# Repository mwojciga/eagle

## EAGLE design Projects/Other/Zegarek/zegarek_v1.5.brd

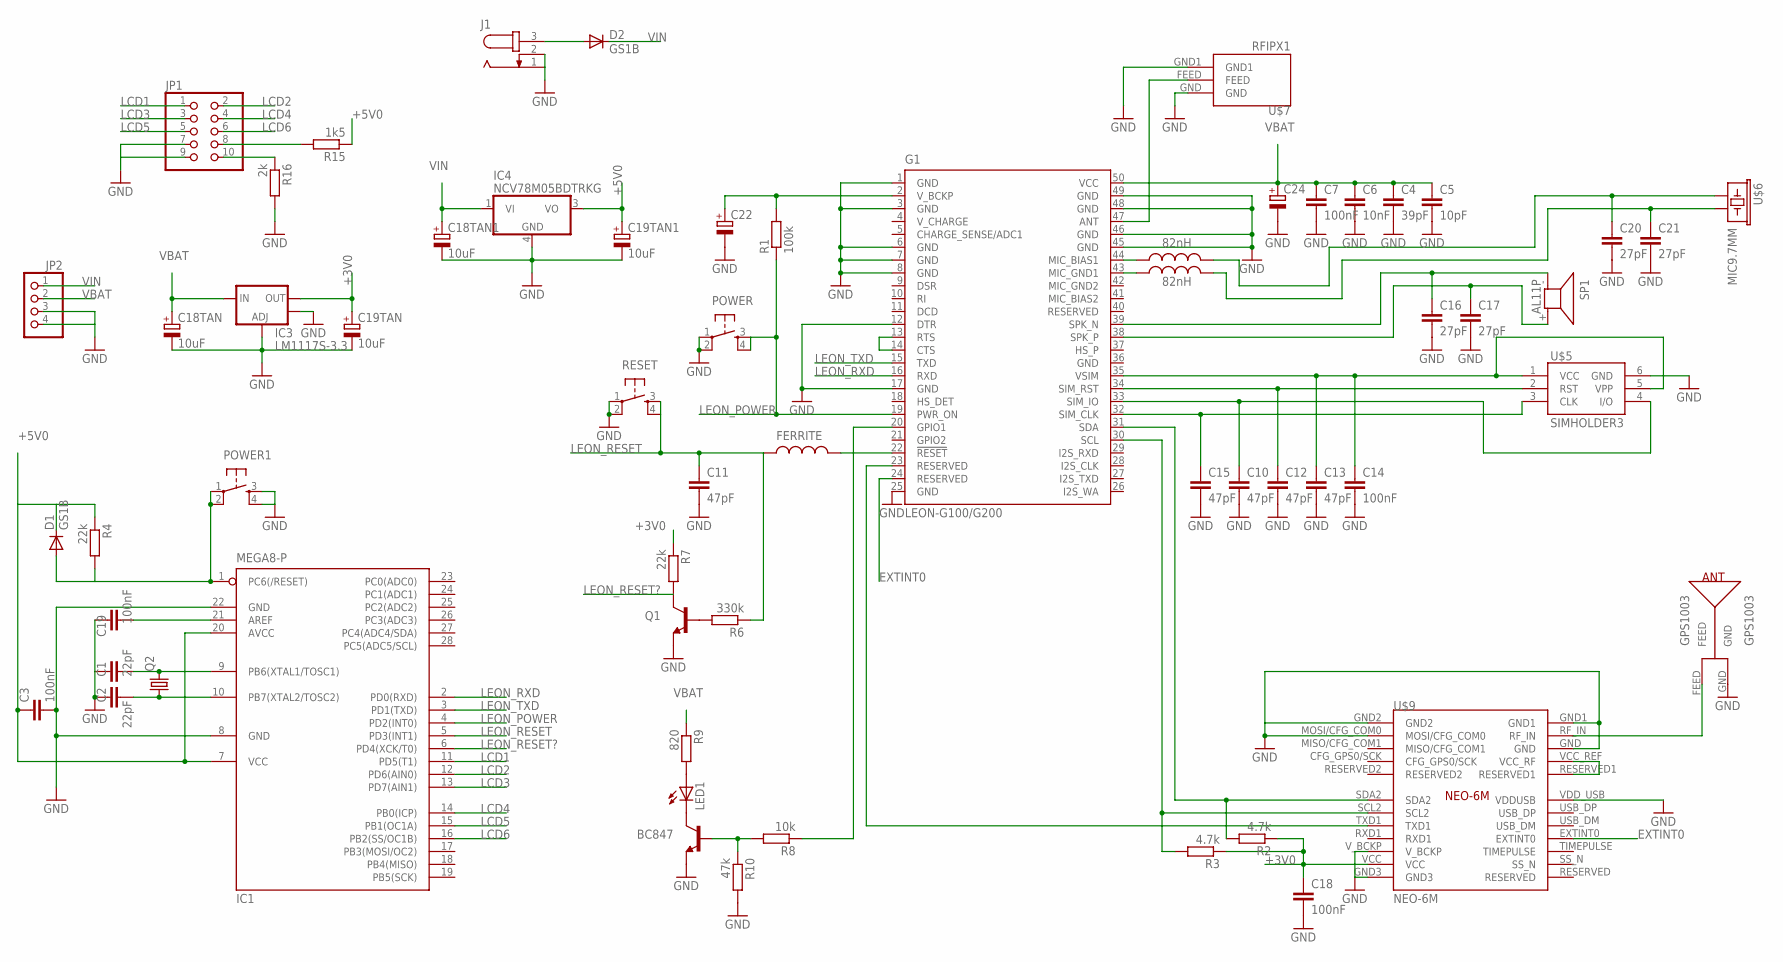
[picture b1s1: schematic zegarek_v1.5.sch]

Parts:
BC847: TRANSISTOR_NPNSOT23; SOT23
C1, C2: 22pF; C0805
C3, C7, C14, C18, C19: 100nF; C0805
C4: 39pF; C0805
C5: 10pF; C0805
C6: 10nF; C0805
C10, C11, C12, C13, C15: 47pF; C0805
C16, C17, C20, C21: 27pF; C0805
C18TAN, C18TAN1, C19TAN, C19TAN1: 10uF; SMC_A
C22, C24: CPOL-EUE2-5; E2-5
D1, D2: GS1B; DO214AC
FERRITE: INDUCTOR0805; 0805
FERRITE1, FERRITE2: 82nH; 0805
G1: LEON-G100/G200
GPS1003: GPS1003
IC1: MEGA8-P; DIL28-3
IC3: LM1117S-3.3; SOT223
IC4: NCV78M05BDTRKG; DPACK_3
J1: JACK-PLUG0; SPC4077
JP1: PINHD-2X5; 2X05
JP2: PINHD-1X4; 1X04
LED1: LEDSMT1206; 1206
POWER, POWER1: TAC_SWITCHSMD; TACTILE_SWITCH_SMD
Q1: TRANSISTOR_NPNSOT23; SOT23
Q2: CRYSTALHC49S; HC49/S
R1: 100k; R0805
R2, R3: 4.7k; R0805
R4, R7: 22k; R0805
R6: 330k; R0805
R8: 10k; R0805
R9: 820; R0805
R10: 47k; R0805
R15: 1k5; R0805
R16: 2k; R0805
RESET: TAC_SWITCHSMD; TACTILE_SWITCH_SMD
SP1: AL11P
U$5: SIMHOLDER3
U$6: MIC9.7MM; MIC-9.7MM
U$7: RFIPX1; RF-IPX1
U$9: NEO-6M

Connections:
+3V0: C18.1, C19TAN.+, IC3.2 (OUT), R2.1, R3.1, R7.1, U$9.VCC
+5V0: C3.1, C19TAN1.+, D1.C, IC1.7 (VCC), IC1.20 (AVCC), IC4.3 (VO), R4.1, R15.1
EXTINT0: G1.24 (RESERVED), U$9.EXTINT0
GND: BC847.2 (E), C1.1, C2.1, C3.2, C4.2, C5.2, C6.2, C7.2, C10.2, C11.2, C12.2, C13.2, C14.2, C15.2, C16.2, C17.2, C18.2, C18TAN.-, C18TAN1.-, C19.2, C19TAN.-, C19TAN1.-, C20.2, C21.2, C22.-, C24.-, G1.1 (GND), G1.3 (GND), G1.6 (GND), G1.7 (GND), G1.8 (GND), G1.12 (DTR), G1.17 (GND), G1.25 (GND), G1.36 (GND), G1.45 (GND), G1.46 (GND), G1.48 (GND), G1.49 (GND), GPS1003.GND, IC1.8 (GND), IC1.22 (GND), IC3.1 (ADJ), IC3.4 (OUT), IC4.4 (GND), J1.1, J1.2, JP1.7, JP1.9, JP2.3, POWER.1, POWER.2, POWER1.3, POWER1.4, Q1.2 (E), R10.2, R16.2, RESET.1, RESET.2, U$5.6 (GND), U$7.GND, U$7.GND1, U$9.GND, U$9.GND1, U$9.GND2, U$9.GND3, U$9.MOSI/CFG_COM0, U$9.VDD_USB (VDDUSB), U$9.V_BCKP
LCD1: IC1.11 (PD5(T1)), JP1.1
LCD2: IC1.12 (PD6(AIN0)), JP1.2
LCD3: IC1.13 (PD7(AIN1)), JP1.3
LCD4: IC1.14 (PB0(ICP)), JP1.4
LCD5: IC1.15 (PB1(OC1A)), JP1.5
LCD6: IC1.16 (PB2(SS/OC1B)), JP1.6
LEON_POWER: G1.19 (PWR_ON), IC1.4 (PD2(INT0)), POWER.3, POWER.4, R1.1
LEON_RESET: C11.1, FERRITE.1, IC1.5 (PD3(INT1)), R6.1, RESET.3, RESET.4
LEON_RESET?: IC1.6 (PD4(XCK/T0)), Q1.3 (C), R7.2
LEON_RXD: G1.16 (RXD), IC1.2 (PD0(RXD))
LEON_TXD: G1.15 (TXD), IC1.3 (PD1(TXD))
unnamed: FERRITE.2, G1.22 (!RESET)
unnamed: C2.2, IC1.10 (PB7(XTAL2/TOSC2)), Q2.1
unnamed: C22.+, G1.2 (V_BCKP), R1.2
unnamed: C13.1, C14.1, G1.35 (VSIM), U$5.1 (VCC), U$5.5 (VPP)
unnamed: C15.1, G1.32 (SIM_CLK), U$5.3 (CLK)
unnamed: C12.1, G1.34 (SIM_RST), U$5.2 (RST)
unnamed: C16.1, G1.39 (SPK_N), SP1.- (1)
unnamed: C10.1, G1.33 (SIM_IO), U$5.4 (I/O)
unnamed: C17.1, G1.38 (SPK_P), SP1.+ (2)
unnamed: G1.13 (RTS), G1.14 (CTS)
unnamed: FERRITE1.1, G1.44 (MIC_BIAS1)
unnamed: FERRITE2.1, G1.43 (MIC_GND1)
unnamed: C20.1, FERRITE1.2, U$6.1
unnamed: C21.1, FERRITE2.2, U$6.2
unnamed: Q1.1 (B), R6.2
unnamed: BC847.1 (B), R8.2, R10.1
unnamed: LED1.A, R9.2
unnamed: BC847.3 (C), LED1.C
unnamed: G1.20 (GPIO1), R8.1
unnamed: G1.47 (ANT), U$7.FEED
unnamed: D2.A, J1.3
unnamed: GPS1003.FEED, U$9.RF_IN
unnamed: G1.31 (SDA), R2.2, U$9.SDA2
unnamed: U$9.RESERVED1, U$9.VCC_REF (VCC_RF)
unnamed: G1.30 (SCL), R3.2, U$9.SCL2
unnamed: G1.23 (RESERVED), U$9.TXD1
unnamed: C1.2, IC1.9 (PB6(XTAL1/TOSC1)), Q2.2
unnamed: D1.A, IC1.1 (PC6(/RESET)), POWER1.1, POWER1.2, R4.2
unnamed: C19.1, IC1.21 (AREF)
unnamed: JP1.10, R16.1
unnamed: JP1.8, R15.2
VBAT: C4.1, C5.1, C6.1, C7.1, C18TAN.+, C24.+, G1.50 (VCC), IC3.3 (IN), JP2.2, R9.1
VIN: C18TAN1.+, D2.C, IC4.1 (VI), JP2.1

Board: 2 copper layers, 61 parts (51 on the bottom side), 48 nets, no tracks yet.

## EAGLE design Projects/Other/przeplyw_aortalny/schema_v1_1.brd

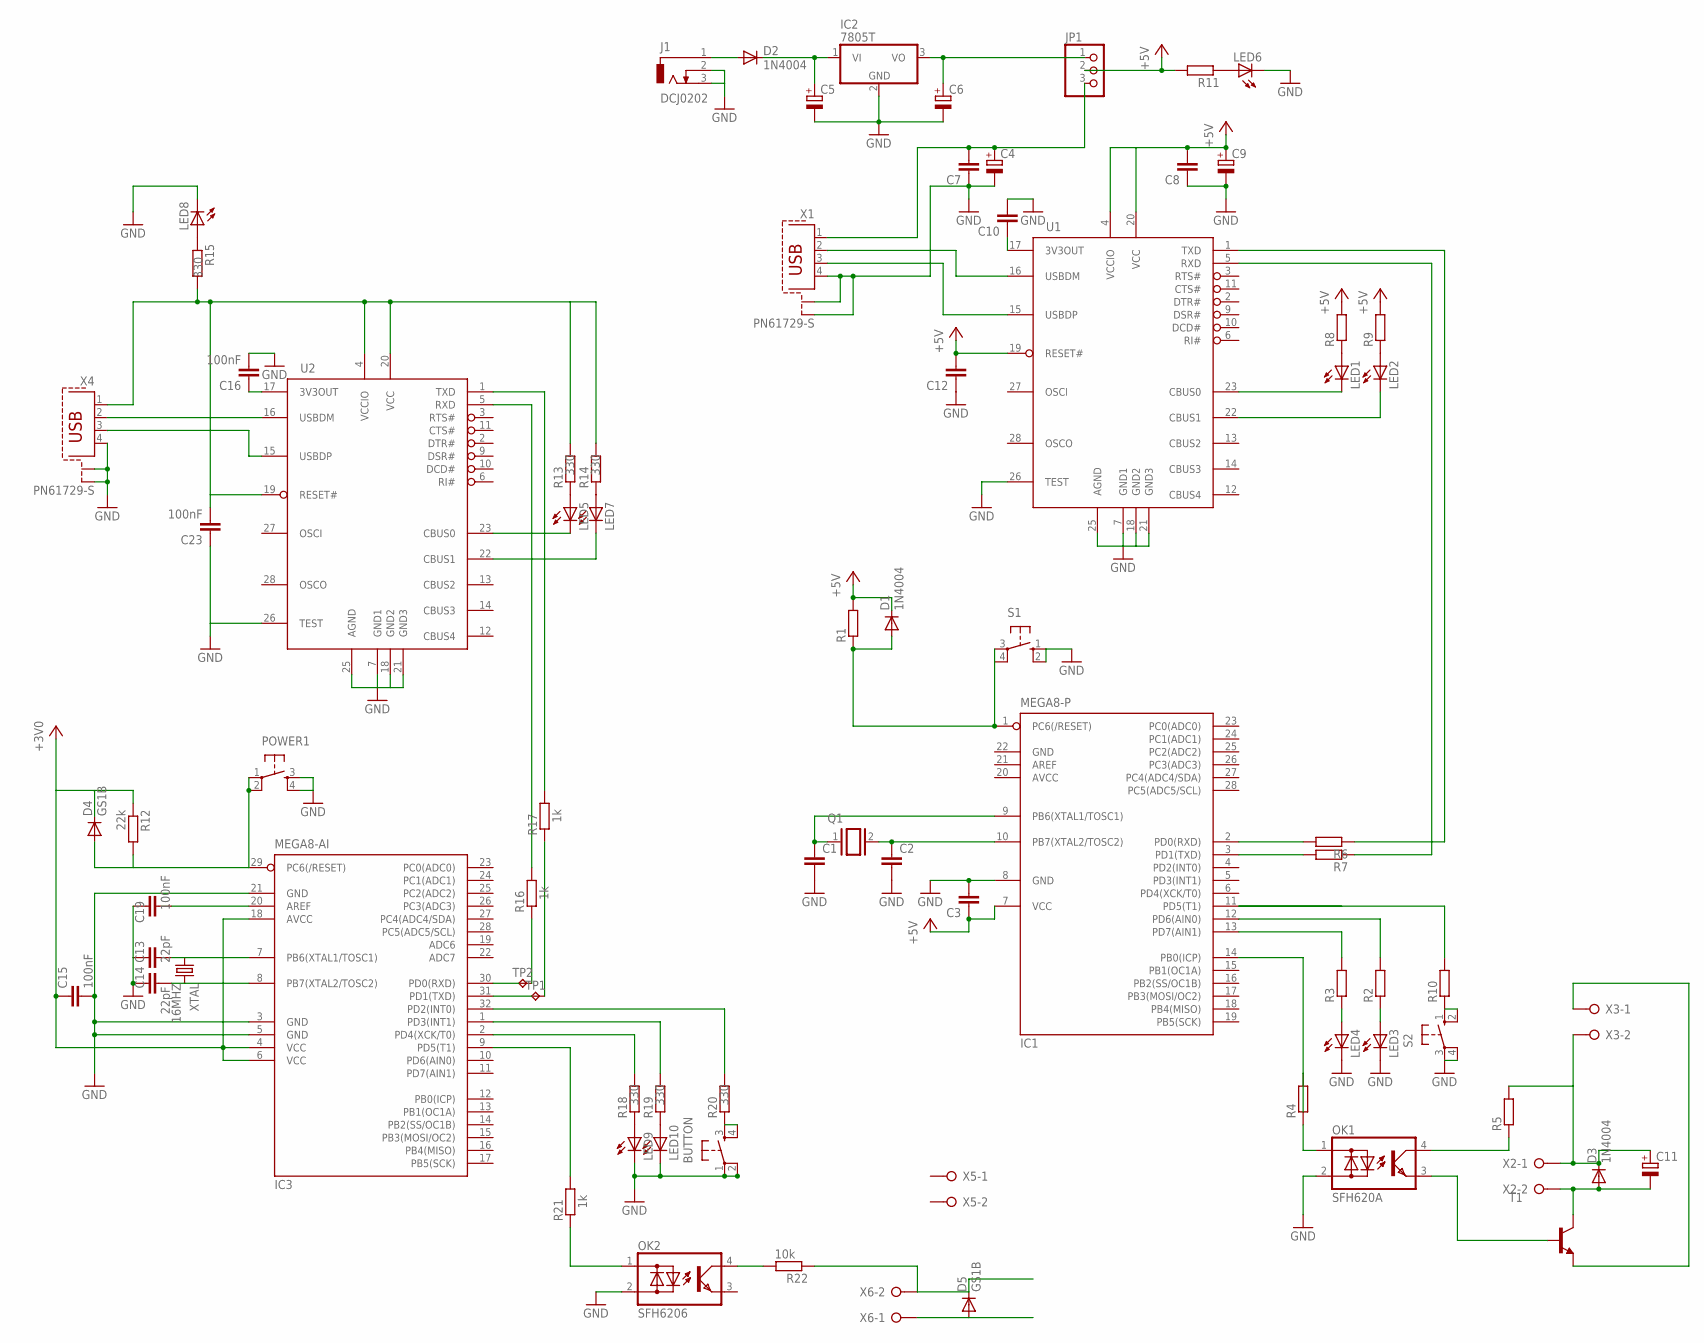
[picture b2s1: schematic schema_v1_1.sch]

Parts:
BUTTON: TAC_SWITCHSMD; TACTILE_SWITCH_SMD
C1, C2, C3, C7, C8, C10, C12: C-EU025-025X050; C025-025X050
C4, C5, C6, C9, C11: CPOL-EUE2.5-5; E2,5-5
C13, C14: 22pF; C0805
C15, C16, C19, C23: 100nF; C0805
D1, D2, D3: 1N4004; DO41-10
D4, D5: GS1B; DO214AC
IC1: MEGA8-P; DIL28-3
IC2: 7805T; TO220H
IC3: MEGA8-AI; TQFP32-08
J1: DCJ0202
JP1: PINHD-1X3/90; 1X03/90
LED1, LED2, LED3, LED4, LED6: LED3MM
LED5, LED7, LED8, LED9, LED10: LEDSMT1206; 1206
OK1: SFH620A; DIL04
OK2: SFH6206; DIL4-SMD
POWER1: TAC_SWITCHSMD; TACTILE_SWITCH_SMD
Q1: XTAL; Q
R1, R2, R3, R4, R5, R6, R7, R8, R9, R10, R11: R-EU_0207/10; 0207/10
R12: 22k; R0805
R13, R14, R15, R18, R19, R20: 330; R0805
R16, R17, R21: 1k; R0805
R22: 10k; R0805
S1, S2: 10-XX; B3F-10XX
T1: -NPN-TO92; TO92
TP1, TP2: TPTP13R; TP13R
U1, U2: FT232RL; SSOP28DB
X1, X4: PN61729-S
X2, X3, X5, X6: W237-02P; W237-132
XTAL: 16MHZ; CSM-7X-DU

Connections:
+3V0: C15.1, D4.C, IC3.4 (VCC), IC3.6 (VCC), IC3.18 (AVCC), R12.1
+5V: C3.1, C8.2, C9.+, C12.2, D1.C, IC1.7 (VCC), JP1.2, R1.2, R8.2, R9.2, R11.2, U1.4 (VCCIO), U1.19 (RESET#), U1.20 (VCC)
AGND: U2.25 (AGND)
AVCC: IC1.20 (AVCC)
GND: BUTTON.1, BUTTON.2, C1.2, C2.2, C3.2, C4.-, C5.-, C6.-, C7.1, C8.1, C9.-, C10.2, C12.1, C13.1, C14.1, C15.2, C16.2, C19.2, C23.1, IC1.8 (GND), IC1.22 (GND), IC2.2 (GND), IC3.3 (GND), IC3.5 (GND), IC3.21 (GND), J1.2, J1.3, LED3.K (C), LED4.K (C), LED6.K (C), LED8.C, LED9.C, LED10.C, OK1.2 (AC2), OK2.2 (AC2), POWER1.3, POWER1.4, S1.1 (S), S1.2 (S1), S2.3, S2.4 (P1), U1.7 (GND1), U1.18 (GND2), U1.21 (GND3), U1.25 (AGND), U1.26 (TEST), U2.26 (TEST), X1.4, X1.S1, X1.S2, X4.4, X4.S1, X4.S2
GND1: U2.7 (GND1)
GND2: U2.18 (GND2)
GND3: U2.21 (GND3)
unnamed: C2.1, IC1.10 (PB7(XTAL2/TOSC2)), Q1.2
unnamed: C1.1, IC1.9 (PB6(XTAL1/TOSC1)), Q1.1
unnamed: D1.A, IC1.1 (PC6(/RESET)), R1.1, S1.3, S1.4 (P1)
unnamed: IC1.13 (PD7(AIN1)), R3.2
unnamed: IC1.14 (PB0(ICP)), R4.2
unnamed: LED3.A, R2.1
unnamed: LED4.A, R3.1
unnamed: R10.1, S2.1 (S), S2.2 (S1)
unnamed: IC1.11 (PD5(T1)), R10.2
unnamed: IC1.12 (PD6(AIN0)), R2.2
unnamed: OK1.4 (C), R5.1
unnamed: OK1.1 (AC1), R4.1
unnamed: D2.A, J1.1
unnamed: C5.+, D2.C, IC2.1 (VI)
unnamed: C6.+, IC2.3 (VO), JP1.1
unnamed: C4.+, C7.2, JP1.3, X1.1
unnamed: LED6.A, R11.1
unnamed: U1.16 (USBDM), X1.2
unnamed: U1.15 (USBDP), X1.3
unnamed: C10.1, U1.17 (3V3OUT)
unnamed: LED1.A, R8.1
unnamed: LED2.A, R9.1
unnamed: LED1.K (C), U1.23 (CBUS0)
unnamed: LED2.K (C), U1.22 (CBUS1)
unnamed: R6.1, U1.1 (TXD)
unnamed: IC1.2 (PD0(RXD)), R6.2
unnamed: IC1.3 (PD1(TXD)), R7.2
unnamed: R7.1, U1.5 (RXD)
unnamed: C11.+, D3.C, R5.2, X2.1, X3.2
unnamed: C11.-, D3.A, T1.3 (C), X2.2
unnamed: OK1.3 (E), T1.2 (B)
unnamed: T1.1 (E), X3.1
unnamed: R16.1, TP2.TP
unnamed: C14.2, IC3.8 (PB7(XTAL2/TOSC2)), XTAL.2
unnamed: C13.2, IC3.7 (PB6(XTAL1/TOSC1)), XTAL.1
unnamed: C19.1, IC3.20 (AREF)
unnamed: D4.A, IC3.29 (PC6(/RESET)), POWER1.1, POWER1.2, R12.2
unnamed: LED5.A, R13.1
unnamed: LED7.A, R14.1
unnamed: LED5.C, U2.23 (CBUS0)
unnamed: LED7.C, U2.22 (CBUS1)
unnamed: R16.2, U2.5 (RXD)
unnamed: R17.2, U2.1 (TXD)
unnamed: BUTTON.3, BUTTON.4, R20.1
unnamed: IC3.2 (PD4(XCK/T0)), R18.2
unnamed: C23.2, R13.2, R14.2, R15.2, U2.4 (VCCIO), U2.19 (RESET#), U2.20 (VCC), X4.1
unnamed: U2.16 (USBDM), X4.2
unnamed: U2.15 (USBDP), X4.3
unnamed: IC3.1 (PD3(INT1)), R19.2
unnamed: LED8.A, R15.1
unnamed: IC3.32 (PD2(INT0)), R20.2
unnamed: C16.1, U2.17 (3V3OUT)
unnamed: LED9.A, R18.1
unnamed: LED10.A, R19.1
unnamed: R17.1, TP1.TP
unnamed: OK2.1 (AC1), R21.1
unnamed: IC3.9 (PD5(T1)), R21.2
unnamed: OK2.4 (C), R22.2
unnamed: D5.C, R22.1, X6.2
unnamed: D5.A, X6.1

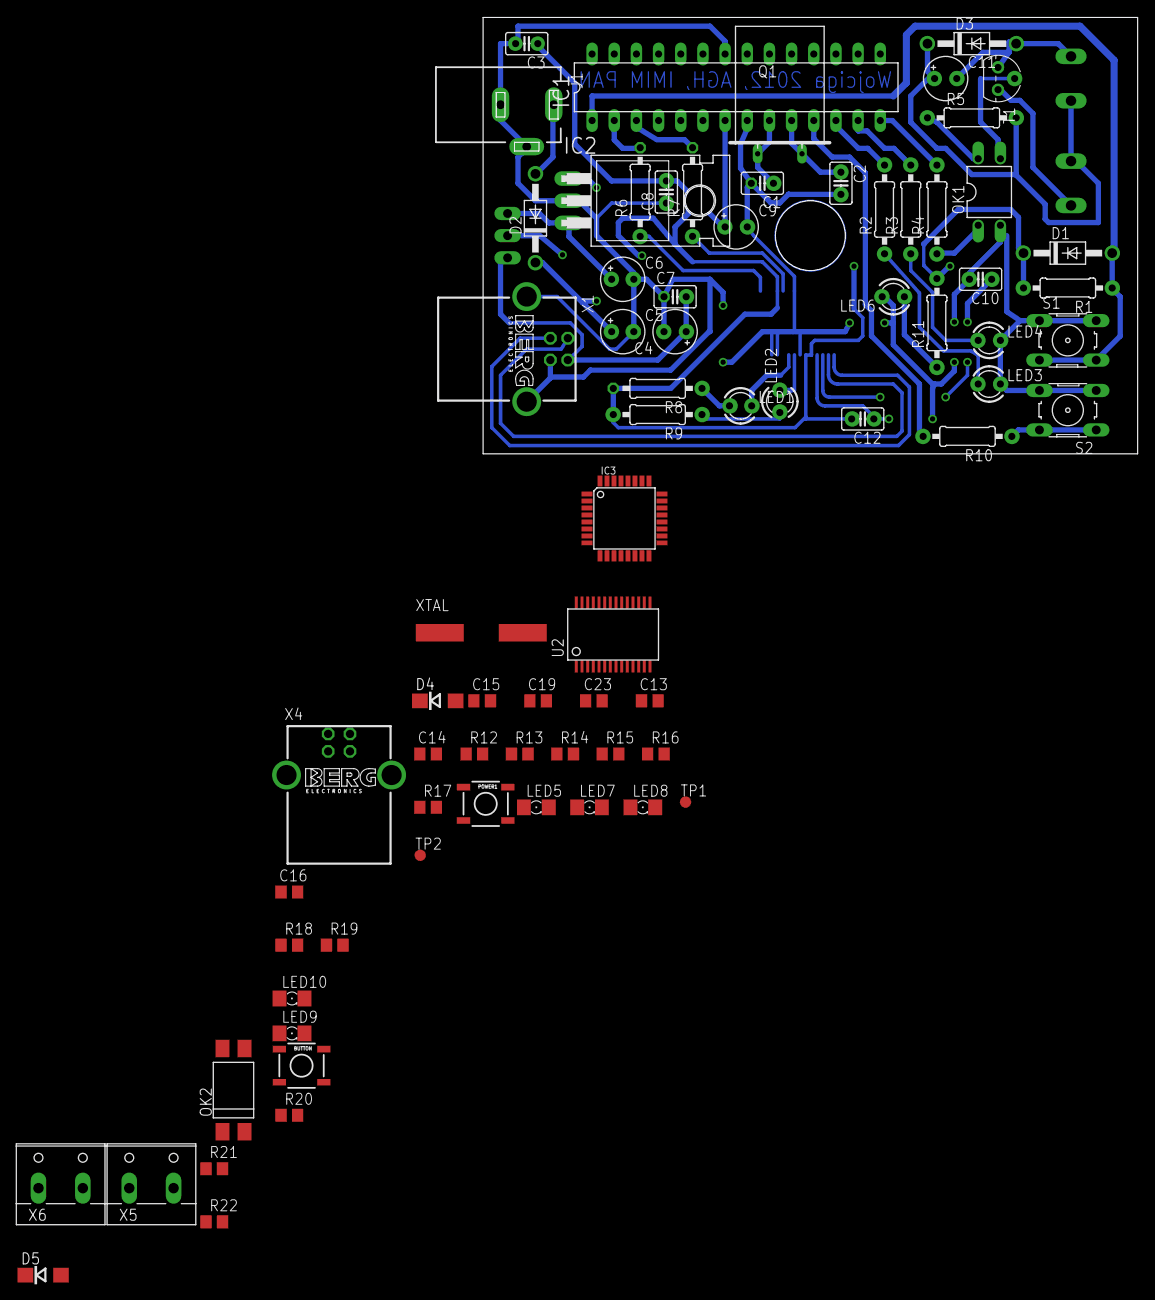
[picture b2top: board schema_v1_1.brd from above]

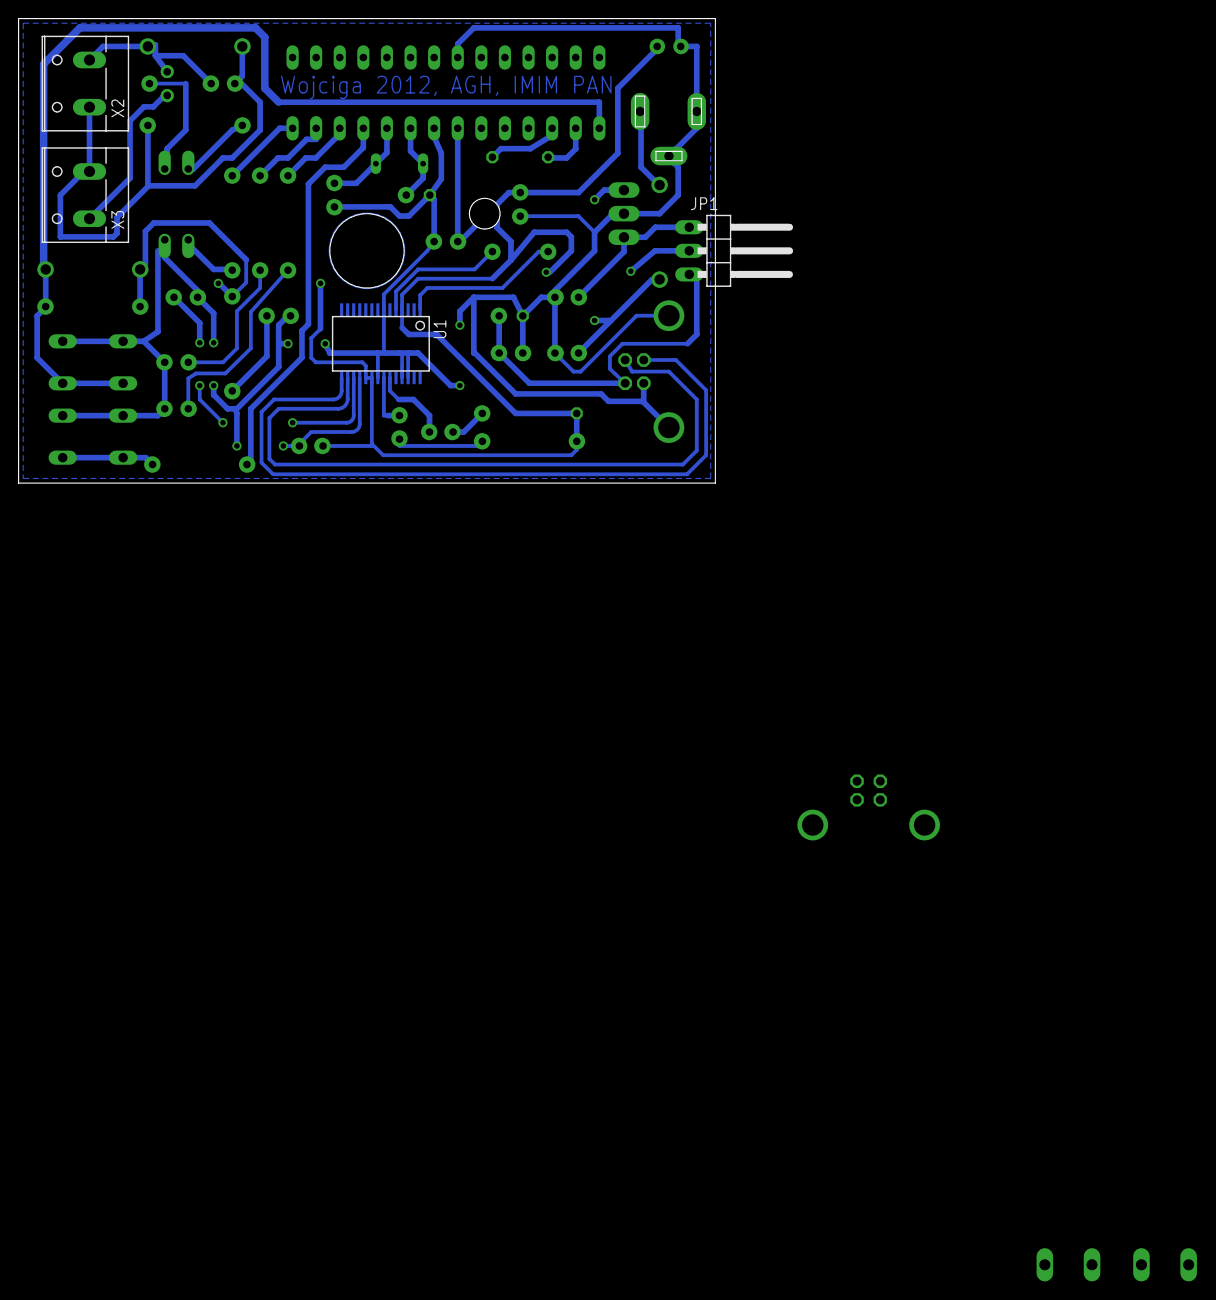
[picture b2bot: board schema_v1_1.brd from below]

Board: 2 copper layers, 75.0 x 50.0 mm, 79 parts (4 on the bottom side), 63 nets.

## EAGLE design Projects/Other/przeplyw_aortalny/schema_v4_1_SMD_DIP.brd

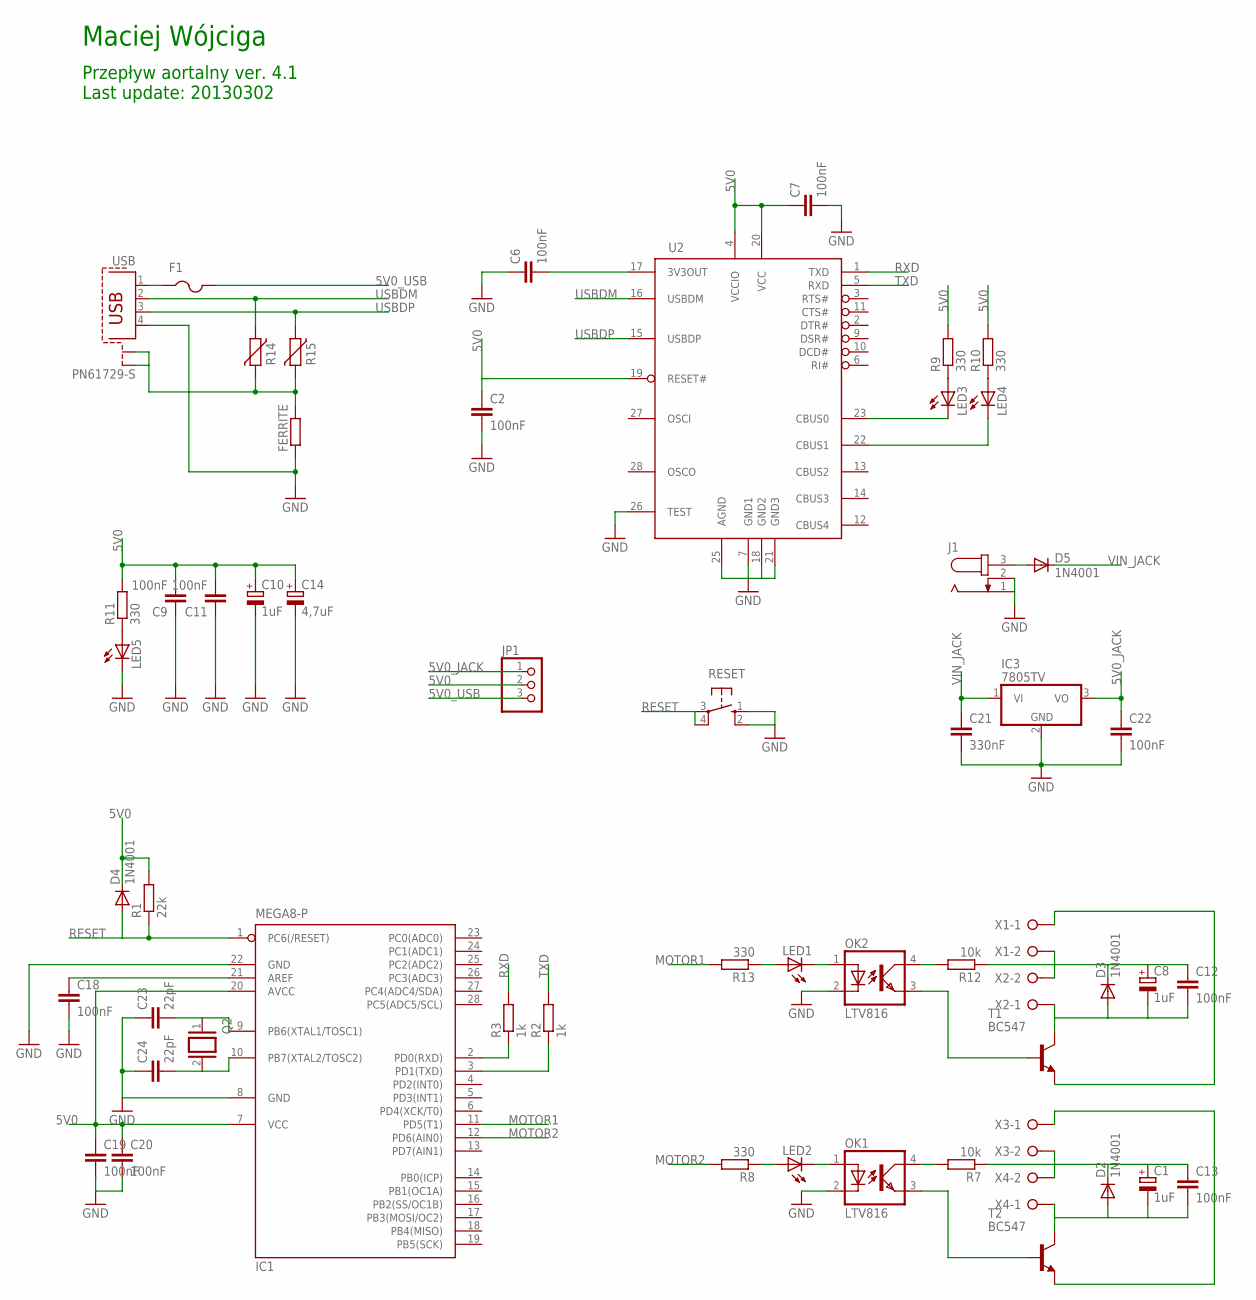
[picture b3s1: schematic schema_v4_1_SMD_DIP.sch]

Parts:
C1, C8, C10: 1uF; E2,5-5
C2, C6, C7: 100nF; C0603K
C9, C11, C12, C13, C19, C20, C22: 100nF; C025-025X050
C14: 4,7uF; E2,5-5
C18: 100nF; C0805
C21: 330nF; C025-025X050
C23, C24: 22pF; C025-025X050
D2, D3, D4, D5: 1N4001; DO41-10
F1: PTCFUSE-1812; 1812
FERRITE: R-EU_M0805; M0805
IC1: MEGA8-P; DIL28-3
IC3: 7805TV; TO220V
J1: JACK-PLUG0; SPC4077
JP1: PINHD-1X3; 1X03
LED1, LED2, LED3, LED4, LED5: LED3MM
OK1, OK2: LTV816; DIL04
Q2: XTAL/S; QS
R1: 22k; 0207/10
R2, R3: 1k; 0207/10
R7, R12: 10k; 0207/10
R8, R9, R10, R11, R13: 330; 0207/10
R14, R15: VARISTORCN0603; CT/CN0603
RESET: 10-XX; B3F-10XX
T1, T2: BC547; TO92
U2: FT232RL; SSOP28DB
USB: PN61729-S
X1, X2, X3, X4: W237-02P; W237-132

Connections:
5V0: C2.1, C7.1, C9.2, C10.+, C11.2, C14.+, C19.1, C20.1, D4.C, IC1.7 (VCC), IC1.20 (AVCC), JP1.2, R1.2, R9.2, R10.2, R11.2, U2.4 (VCCIO), U2.19 (RESET#), U2.20 (VCC)
5V0_JACK: C22.1, IC3.3 (VO), JP1.1
5V0_USB: F1.2, JP1.3
GND: C2.2, C6.1, C7.2, C9.1, C10.-, C11.1, C14.-, C18.2, C19.2, C20.2, C21.2, C22.2, C23.1, C24.1, FERRITE.1, IC1.8 (GND), IC1.22 (GND), IC3.2 (GND), J1.1, J1.2, LED5.K (C), OK1.2 (C), OK2.2 (C), RESET.1 (S), RESET.2 (S1), U2.7 (GND1), U2.18 (GND2), U2.21 (GND3), U2.25 (AGND), U2.26 (TEST), USB.4
MOTOR1: IC1.11 (PD5(T1)), R13.2
MOTOR2: IC1.12 (PD6(AIN0)), R8.2
unnamed: IC1.3 (PD1(TXD)), R2.1
unnamed: IC1.2 (PD0(RXD)), R3.1
unnamed: LED1.A, R13.1
unnamed: LED1.K (C), OK2.1 (A)
unnamed: LED2.A, R8.1
unnamed: LED3.A, R9.1
unnamed: LED4.A, R10.1
unnamed: LED5.A, R11.1
unnamed: C1.+, C13.1, D2.C, R7.1, X3.2, X4.2
unnamed: LED2.K (C), OK1.1 (A)
unnamed: C1.-, C13.2, D2.A, T2.3 (C), X4.1
unnamed: OK1.3 (EMIT), T2.2 (B)
unnamed: OK2.4 (COL), R12.2
unnamed: T1.1 (E), X1.1
unnamed: C8.+, C12.1, D3.C, R12.1, X1.2, X2.2
unnamed: C8.-, C12.2, D3.A, T1.3 (C), X2.1
unnamed: OK2.3 (EMIT), T1.2 (B)
unnamed: F1.1, USB.1
unnamed: FERRITE.2, R14.2, R15.2, USB.S1, USB.S2
unnamed: C18.1, IC1.21 (AREF)
unnamed: D5.A, J1.3
unnamed: C23.2, IC1.9 (PB6(XTAL1/TOSC1)), Q2.1
unnamed: C24.2, IC1.10 (PB7(XTAL2/TOSC2)), Q2.2
unnamed: LED3.K (C), U2.23 (CBUS0)
unnamed: LED4.K (C), U2.22 (CBUS1)
unnamed: C6.2, U2.17 (3V3OUT)
unnamed: OK1.4 (COL), R7.2
unnamed: T2.1 (E), X3.1
RESET: D4.A, IC1.1 (PC6(/RESET)), R1.1, RESET.3, RESET.4 (P1)
RXD: R3.2, U2.1 (TXD)
TXD: R2.2, U2.5 (RXD)
USBDM: R14.1, U2.16 (USBDM), USB.2
USBDP: R15.1, U2.15 (USBDP), USB.3
VIN_JACK: C21.1, D5.C, IC3.1 (VI)

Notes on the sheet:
Maciej Wójciga
Przepływ aortalny ver. 4.1 Last update: 20130302

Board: 2 copper layers, 57 parts (9 on the bottom side), 40 nets, no tracks yet.

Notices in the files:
parts and their libraries:
SparkFun: Licensing: CC v3.0 Share-Alike You are welcome to use this library for commercial purposes.
